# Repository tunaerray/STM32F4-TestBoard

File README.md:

# STM32F405RGT6 Test Board Hardware Design

A custom-designed embedded development and test board based on the **STM32F405RGT6** microcontroller.
This project focuses on creating a reliable, protected, and programmable STM32-based hardware platform with multiple communication interfaces and a robust power architecture.

## Overview

The board was designed as a programmable STM32F405RGT6-based embedded development platform. It includes common communication interfaces such as **UART**, **I2C**, and **USB**, along with power input protection and programming support.

The hardware design also includes protection mechanisms for safer operation, such as reverse polarity protection, overcurrent protection, and USB ESD protection.

## Features

* STM32F405RGT6 microcontroller
* UART communication interface
* I2C communication interface
* USB interface
* SWD programming support
* External 16 MHz clock circuit
* 12V external power input support
* USB 5V power input support
* Reverse polarity protection
* Overcurrent protection
* USB ESD protection
* Buck converter-based power stage
* 4-layer PCB design
* Signal integrity and power integrity considerations

## Hardware Design

The board includes two different power input paths:

* **12V external input**
* **USB 5V input**

Both input paths were designed with protection in mind. The external power input includes reverse polarity and overcurrent protection, while the USB line includes ESD protection to improve reliability during development and testing.

A buck converter-based power stage is used to generate a safe and stable voltage level for the STM32 microcontroller and peripheral circuits.

## PCB Design

The PCB was designed as a **4-layer board** to improve routing quality, power distribution, and signal integrity.
The layout was created by considering:

* Power integrity
* Signal integrity
* Proper decoupling
* Short and clean clock routing
* Stable MCU power delivery
* USB and communication line protection

## Images

### PCB Front

### PCB Back

## Project Purpose

The main purpose of this project is to create a reliable STM32F405RGT6-based test and development board that can be used for embedded software development, peripheral testing, and hardware validation.

## Technologies Used

* STM32F405RGT6
* KiCad
* 4-layer PCB design
* Buck converter power stage
* UART
* I2C
* USB
* SWD programming interface

## Status

Hardware design completed and PCB files prepared for production.

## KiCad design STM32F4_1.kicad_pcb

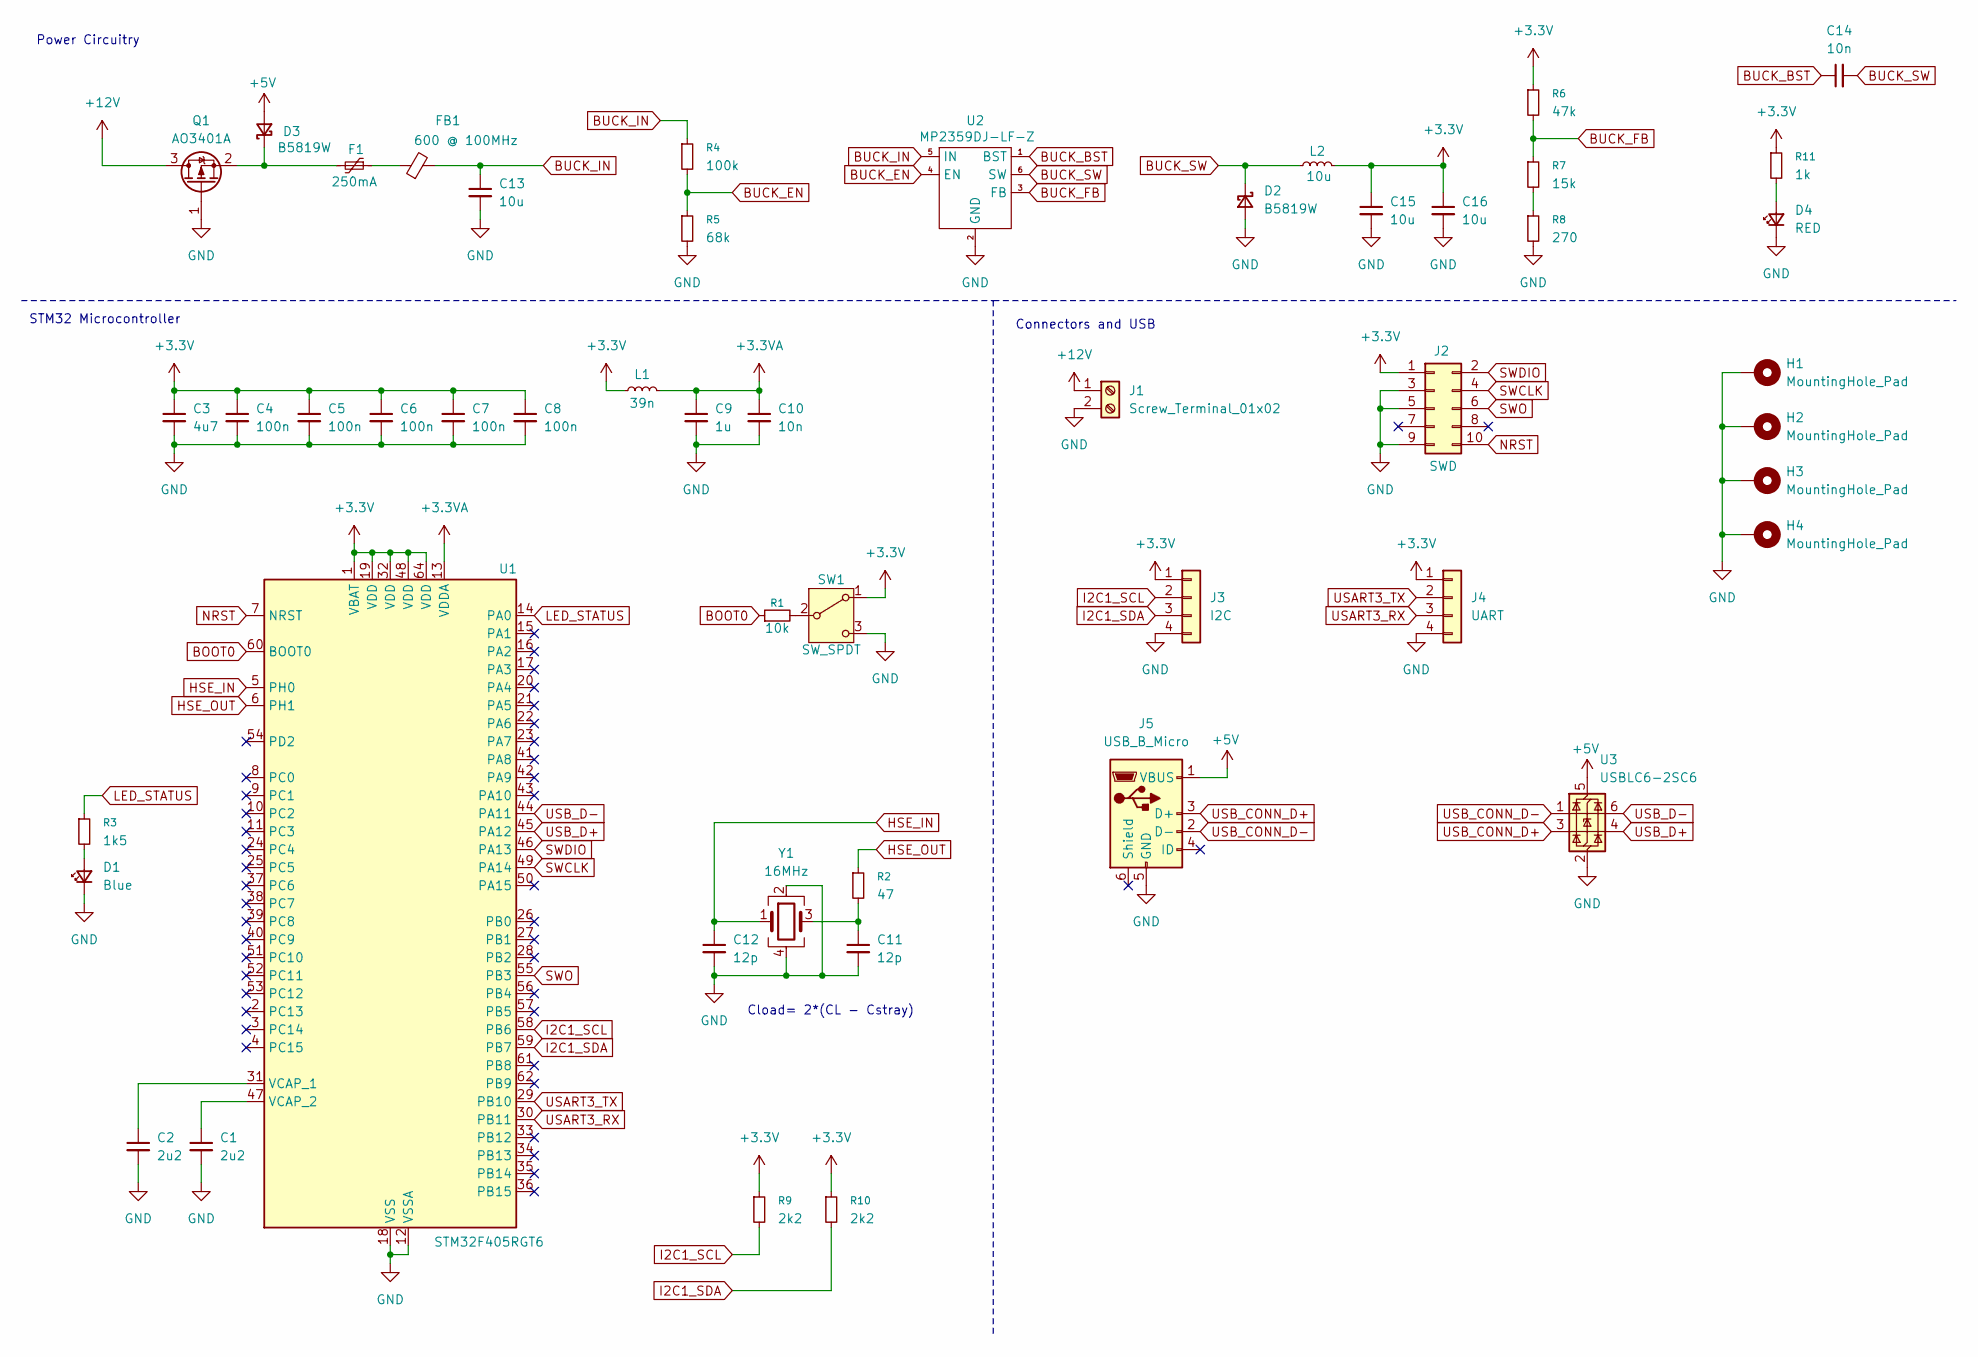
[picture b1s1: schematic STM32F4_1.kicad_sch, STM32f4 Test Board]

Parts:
C1, C2: 2u2; C_0603_1608Metric
C3: 4u7; C_0603_1608Metric
C4, C5, C6, C7, C8: 100n; C_0402_1005Metric
C9: 1u; C_0402_1005Metric
C10: 10n; C_0402_1005Metric
C11, C12: 12p; C_0402_1005Metric
C13, C15, C16: 10u; C_1206_3216Metric
C14: 10n; C_0603_1608Metric
D1: Blue; LED_0603_1608Metric
D2, D3: B5819W; D_SOD-123
D4: RED; LED_0603_1608Metric
F1: 250mA; Fuse_1206_3216Metric
FB1: 600 @ 100MHz; L_0805_2012Metric
H1, H2, H3, H4: MountingHole_Pad; MountingHole_4.3mm_M4_Pad_Via
J1: Screw_Terminal_01x02; TerminalBlock_Phoenix_PT-1,5-2-3.5-H_1x02_P3.50mm_Horizontal
J2: SWD; PinHeader_2x05_P1.27mm_Vertical_SMD
J3: I2C; Molex_PicoBlade_53048-0410_1x04_P1.25mm_Horizontal
J4: UART; Molex_PicoBlade_53048-0410_1x04_P1.25mm_Horizontal
J5: USB_B_Micro; USB_Micro-B_Amphenol_10118193-0002LF_Horizontal
L1: 39n; L_0402_1005Metric
L2: 10u; L_Sunlord_MWSA0518S
Q1: AO3401A; SOT-23
R1: 10k; R_0402_1005Metric
R2: 47; R_0402_1005Metric
R3: 1k5; R_0603_1608Metric
R4: 100k; R_0603_1608Metric
R5: 68k; R_0603_1608Metric
R6: 47k; R_0603_1608Metric
R7: 15k; R_0603_1608Metric
R8: 270; R_0603_1608Metric
R9, R10: 2k2; R_0402_1005Metric
R11: 1k; R_0603_1608Metric
SW1: SW_SPDT; SW_SPDT_PCM12
U1: STM32F405RGT6; LQFP-64_10x10mm_P0.5mm
U2: MP2359DJ-LF-Z; TSOT-23-6
U3: USBLC6-2SC6; SOT-23-6
Y1: 16MHz; Crystal_SMD_3225-4Pin_3.2x2.5mm

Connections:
+3.3V: C3.1, C4.1, C5.1, C6.1, C7.1, C8.1, C15.1, C16.1, J2.1, J3.1, J4.1, L1.1, L2.2, R6.1, R9.1, R10.1, R11.1, SW1.1 (A), U1.1 (VBAT), U1.19 (VDD), U1.32 (VDD), U1.48 (VDD), U1.64 (VDD)
+3.3VA: C9.1, C10.1, L1.2, U1.13 (VDDA)
+5V: D3.2 (A), J5.1 (VBUS), U3.5 (VBUS)
+12V: J1.1, Q1.3 (D)
BOOT0: R1.1, U1.60 (BOOT0)
BUCK_BST: C14.1, U2.1 (BST)
BUCK_EN: R4.2, R5.1, U2.4 (EN)
BUCK_FB: R6.2, R7.1, U2.3 (FB)
BUCK_IN: C13.1, FB1.2, R4.1, U2.5 (IN)
BUCK_SW: C14.2, D2.1 (K), L2.1, U2.6 (SW)
GND: C1.2, C2.2, C3.2, C4.2, C5.2, C6.2, C7.2, C8.2, C9.2, C10.2, C11.2, C12.2, C13.2, C15.2, C16.2, D1.1 (K), D2.2 (A), D4.1 (K), H1.1, H2.1, H3.1, H4.1, J1.2, J2.3, J2.5, J2.9, J3.4, J4.4, J5.5 (GND), Q1.1 (G), R5.2, R8.2, SW1.3 (C), U1.12 (VSSA), U1.18 (VSS), U1.63 (VSS), U2.2 (GND), U3.2 (GND), Y1.2, Y1.4
HSE_IN: C12.1, U1.5 (PH0), Y1.1
HSE_OUT: R2.1, U1.6 (PH1)
I2C1_SCL: J3.2, R9.2, U1.58 (PB6)
I2C1_SDA: J3.3, R10.2, U1.59 (PB7)
LED_STATUS: R3.1, U1.14 (PA0)
NRST: J2.10, U1.7 (NRST)
unnamed: C11.1, R2.2, Y1.3
unnamed: D1.2 (A), R3.2
unnamed: D3.1 (K), F1.2, Q1.2 (S)
unnamed: D4.2 (A), R11.2
unnamed: F1.1, FB1.1
unnamed: R7.2, R8.1
unnamed: R1.2, SW1.2 (B)
unnamed: C2.1, U1.31 (VCAP_1)
unnamed: C1.1, U1.47 (VCAP_2)
SWCLK: J2.4, U1.49 (PA14)
SWDIO: J2.2, U1.46 (PA13)
SWO: J2.6, U1.55 (PB3)
USART3_RX: J4.3, U1.30 (PB11)
USART3_TX: J4.2, U1.29 (PB10)
USB_CONN_D+: J5.3 (D+), U3.3 (I/O2)
USB_CONN_D-: J5.2 (D-), U3.1 (I/O1)
USB_D+: U1.45 (PA12), U3.4 (I/O2)
USB_D-: U1.44 (PA11), U3.6 (I/O1)

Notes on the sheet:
STM32 Microcontroller
Power Circuitry
Connectors and USB
Cload= 2*(CL - Cstray)

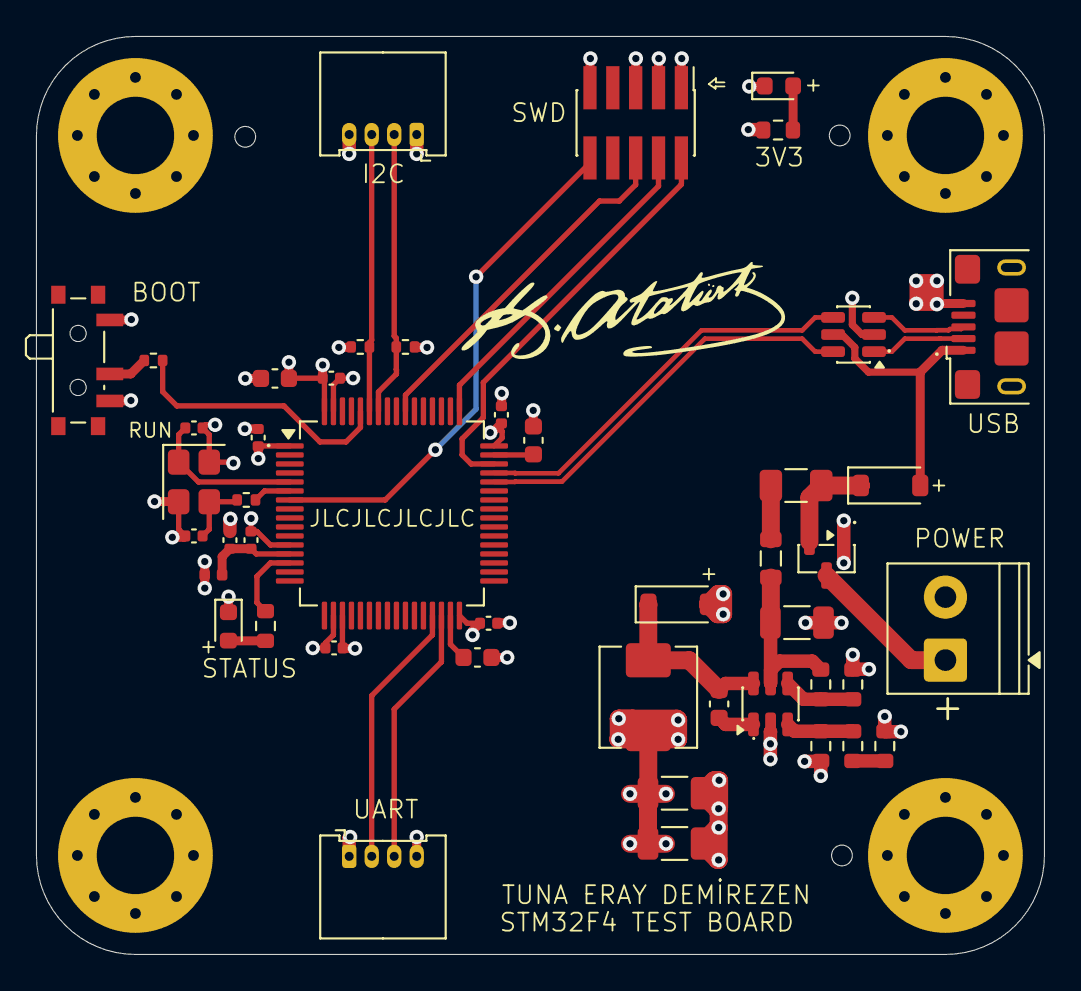
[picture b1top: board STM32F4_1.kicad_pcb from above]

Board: 4 copper layers, 56.0 x 51.0 mm, 50 parts (0 on the bottom side), 35 nets.

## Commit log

2026-05-30 Create images
2026-05-30 Add PCB images
2026-06-03 Add README for STM32F405RGT6 Test Board
    This README.md provides an overview of the STM32F405RGT6 test board hardware design, detailing features, hardware design considerations, PCB design, and project purpose.
